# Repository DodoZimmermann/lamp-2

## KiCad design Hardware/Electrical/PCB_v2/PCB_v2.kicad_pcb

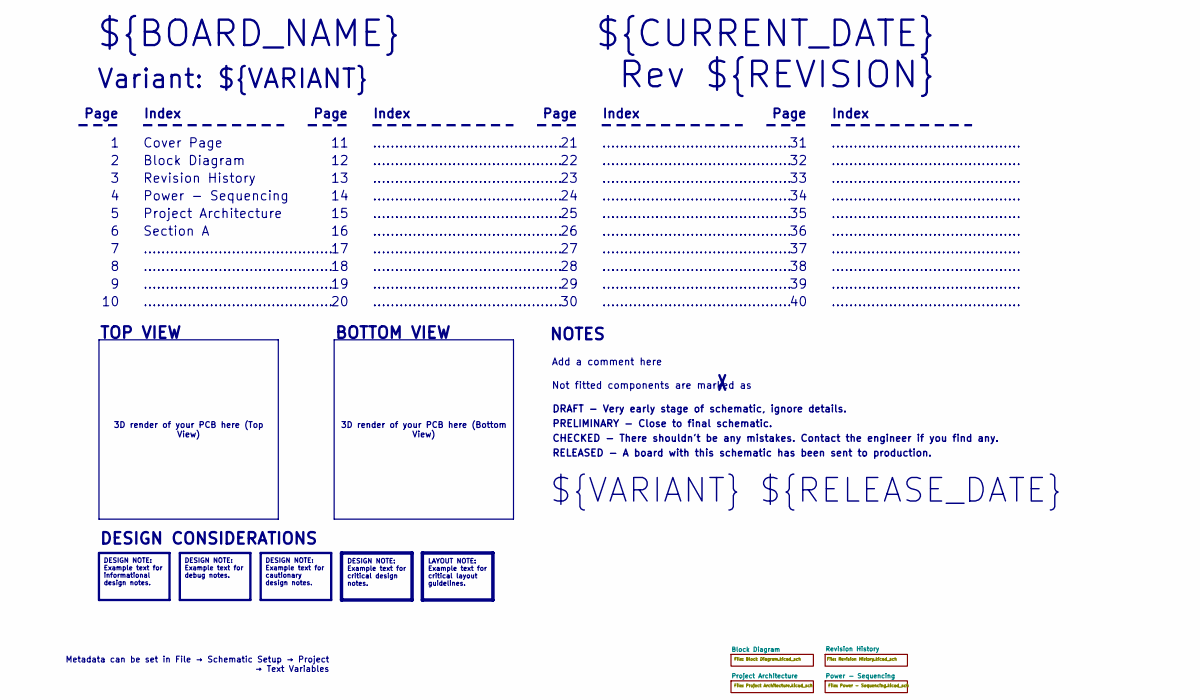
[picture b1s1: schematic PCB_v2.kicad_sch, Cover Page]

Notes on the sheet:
BOTTOM VIEW
...........................................
RELEASED - A board with this schematic has been sent to production.
Page
TOP VIEW
Not fitted components are marked as
Index
PRELIMINARY - Close to final schematic.
${VARIANT} ${RELEASE_DATE}
Power - Sequencing
${CURRENT_DATE}
Variant: ${VARIANT}
Rev ${REVISION}
Project Architecture
${BOARD_NAME}
DRAFT - Very early stage of schematic, ignore details.
Section A
Block Diagram
Add a comment here
Cover Page
NOTES
Revision History
CHECKED - There shouldn't be any mistakes. Contact the engineer if you find any.
DESIGN CONSIDERATIONS
3D render of your PCB here (Bottom View)
3D render of your PCB here (Top View)
Metadata can be set in File → Schematic Setup → Project → Text Variables
DESIGN NOTE: Example text for informational design notes.
LAYOUT NOTE: Example text for critical layout guidelines.
DESIGN NOTE: Example text for cautionary design notes.
DESIGN NOTE: Example text for debug notes.
DESIGN NOTE: Example text for critical design notes.

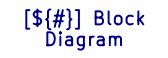
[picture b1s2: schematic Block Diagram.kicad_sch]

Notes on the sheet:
[${#}] ${TITLE}

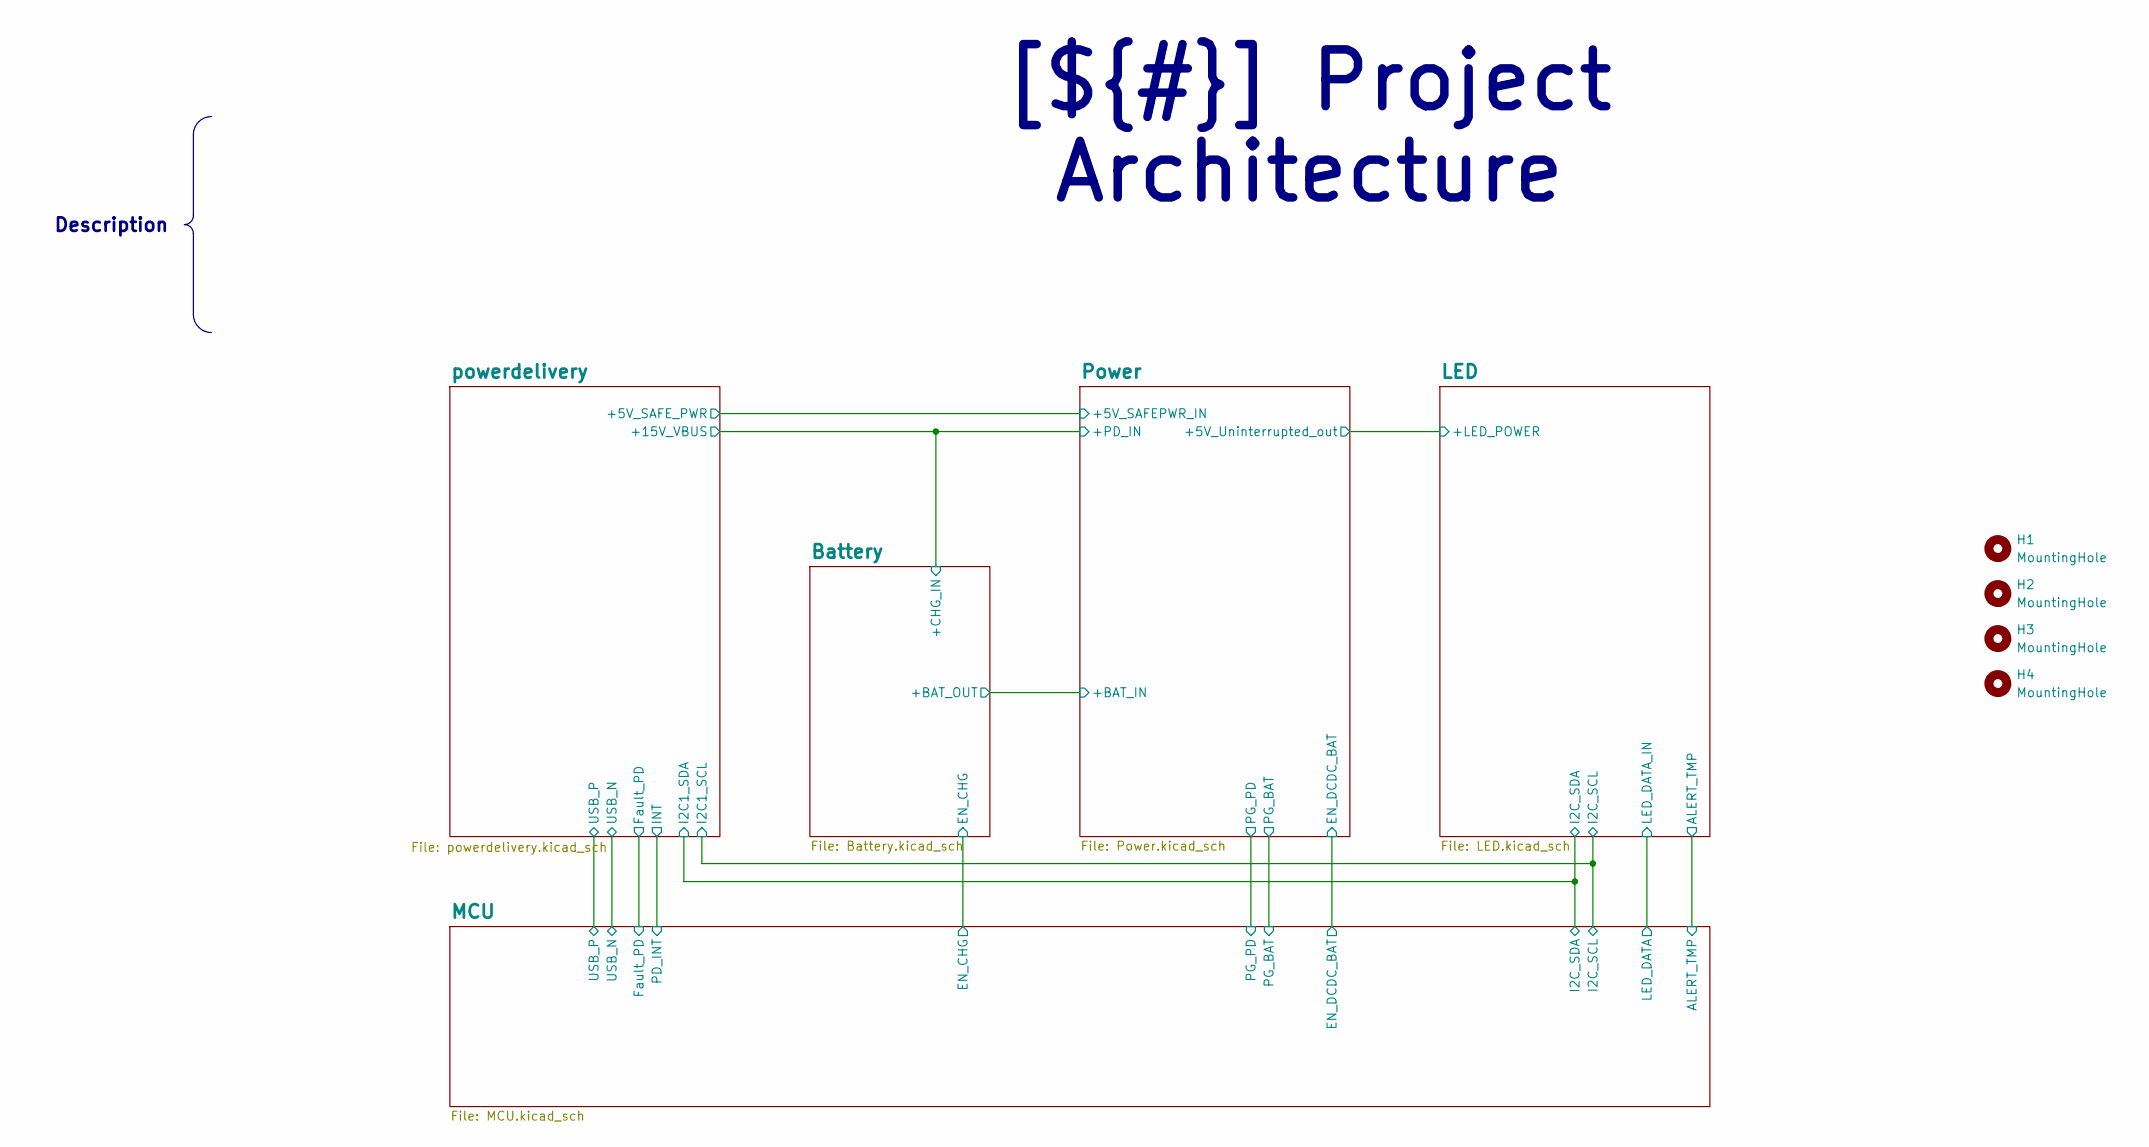
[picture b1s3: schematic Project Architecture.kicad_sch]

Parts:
H1, H2, H3, H4: MountingHole; MountingHole_2.7mm_M2.5

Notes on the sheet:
Description
[${#}] ${TITLE}

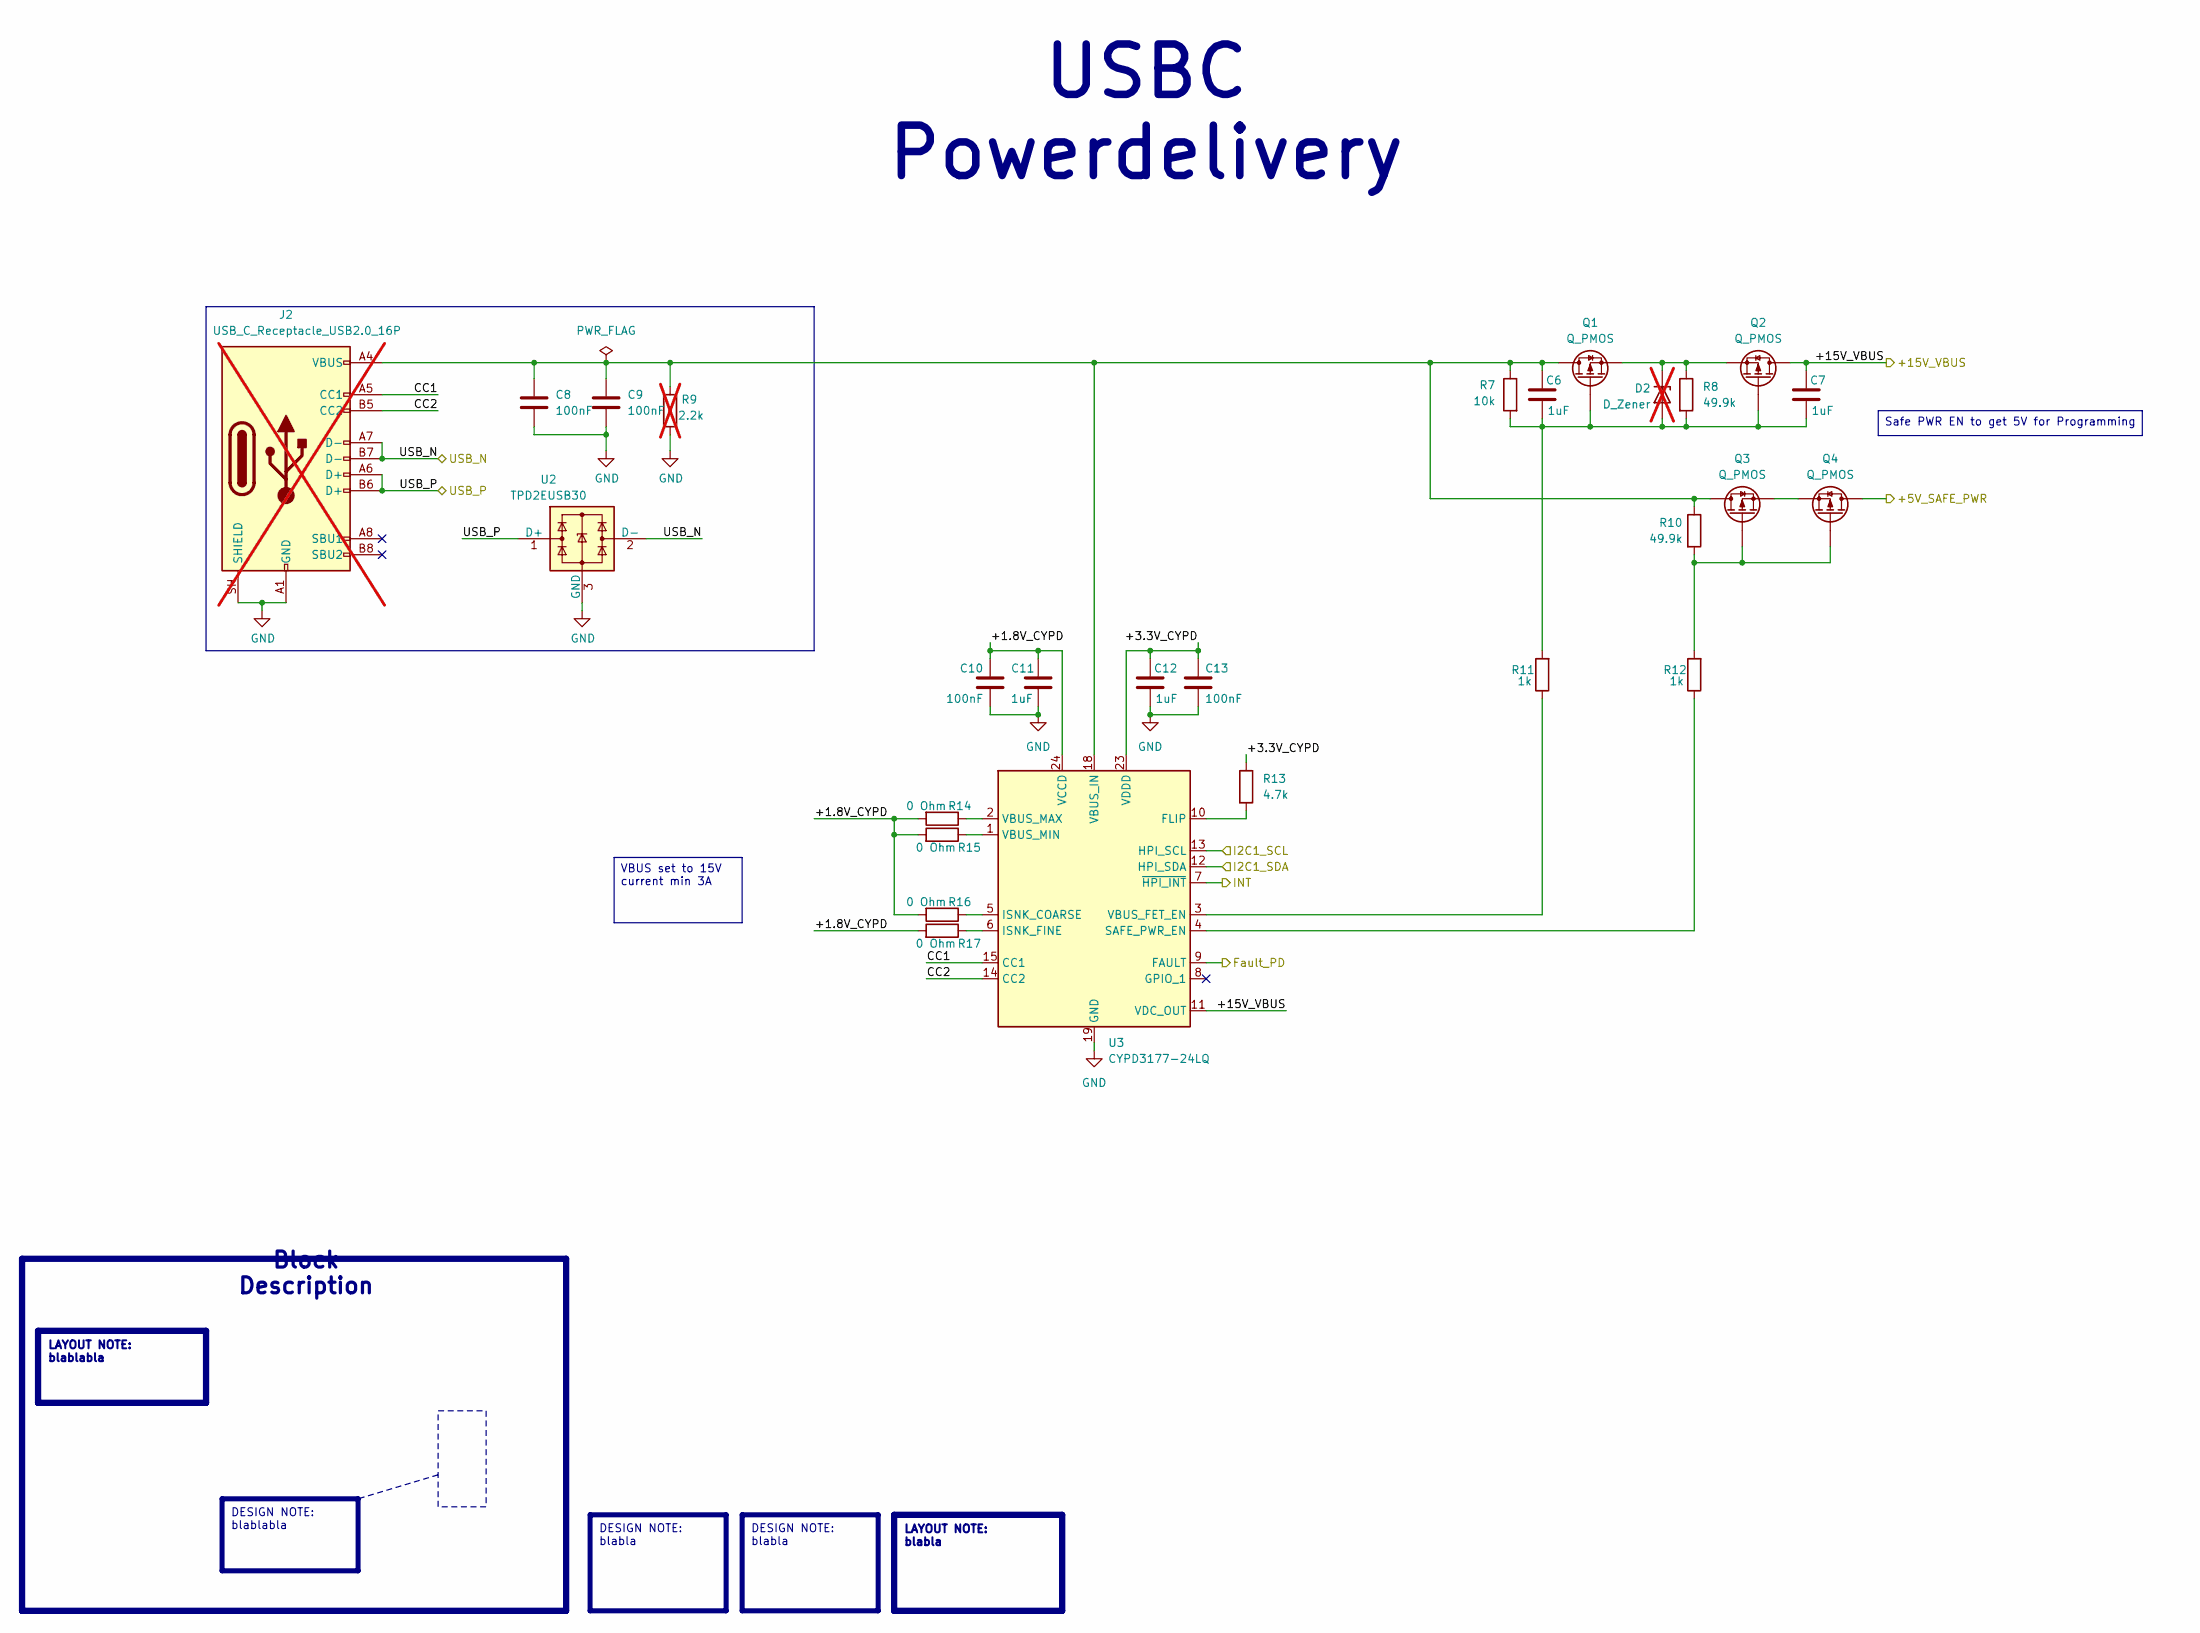
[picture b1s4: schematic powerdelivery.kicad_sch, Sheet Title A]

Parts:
C6, C7, C11, C12: 1uF; C_0603_1608Metric; Manufacturer Part Number CC0603KRX7R9BB105; LCSC Part # C15849
C8, C9, C10, C13: 100nF; C_0603_1608Metric; Manufacturer Part Number 885012206095; LCSC Part # C14663
D2: D_Zener; D_SOD-323; not fitted
J2: USB_C_Receptacle_USB2.0_16P; USB_C_Receptacle_GCT_USB4105-xx-A_16P_TopMnt_Horizontal; Manufacturer Part Number USB4105-GF-A; not fitted
Q1, Q2, Q3, Q4: Q_PMOS; PowerPAK_SO-8; Manufacturer Part Number SI7149ADP-T1-GE3; LCSC Part # C554002
R7: 10k; R_0603_1608Metric; Manufacturer Part Number ERJ-PB3B1002V; LCSC Part # C25804
R8, R10: 49.9k; R_0603_1608Metric; LCSC Part # C23184
R9: 2.2k; R_0603_1608Metric; Manufacturer Part Number RC0603FR-072K2L; LCSC Part # C114662; not fitted
R11, R12: 1k; R_0603_1608Metric; Manufacturer Part Number RC0603FR-071KL; LCSC Part # C21190
R13: 4.7k; R_0603_1608Metric; LCSC Part # C23162
R14, R15, R16, R17: 0 Ohm; R_0603_1608Metric; Manufacturer Part Number RC0603JR-070RL; LCSC Part # C21189
U2: TPD2EUSB30; Texas_DRT-3; Manufacturer Part Number TPD2EUSB30ADRTR; LCSC Part # C97502
U3: CYPD3177-24LQ; QFN-24-1EP_4x4mm_P0.5mm_EP2.75x2.75mm; LCSC Part # C2959321

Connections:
/Project Architecture/LED/I2C_SCL: U3.13 (HPI_SCL); also elsewhere on the board
/Project Architecture/LED/I2C_SDA: U3.12 (HPI_SDA); also elsewhere on the board
/Project Architecture/MCU/Fault_PD: U3.9 (FAULT); also elsewhere on the board
/Project Architecture/MCU/PD_INT: U3.7 (~HPI_INT); also elsewhere on the board
/Project Architecture/Power/+5V_SAFEPWR_IN: Q4.D; also elsewhere on the board
/Project Architecture/powerdelivery/+1.8V_CYPD: C10.2, C11.2, R14.2, R15.2, R16.2, R17.2, U3.24 (VCCD)
/Project Architecture/powerdelivery/+3.3V_CYPD: C12.2, C13.2, R13.1, U3.23 (VDDD)
/Project Architecture/powerdelivery/+15V_VBUS: C7.2, Q2.D, U3.11 (VDC_OUT); also elsewhere on the board
/Project Architecture/powerdelivery/CC1: J2.A5 (CC1), U3.15 (CC1)
/Project Architecture/powerdelivery/CC2: J2.B5 (CC2), U3.14 (CC2)
/Project Architecture/powerdelivery/USB_N: J2.A7 (D-), J2.B7 (D-), U2.2 (D-); also elsewhere on the board
/Project Architecture/powerdelivery/USB_P: J2.A6 (D+), J2.B6 (D+), U2.1 (D+); also elsewhere on the board
GND: C8.1, C9.1, C10.1, C11.1, C12.1, C13.1, J2.A1 (GND), J2.A12 (GND), J2.B1 (GND), J2.B12 (GND), J2.SH (SHIELD), R9.1, U2.3 (GND), U3.19 (GND), U3.22 (GND), U3.25 (GND); also elsewhere on the board
unnamed: C6.1, C7.1, D2.2 (A), Q1.G, Q2.G, R7.2, R8.2, R11.2
unnamed: D2.1 (K), Q1.S, Q2.S, R8.1
unnamed: Q3.G, Q4.G, R10.2, R12.2
unnamed: Q3.S, Q4.S
unnamed: R13.2, U3.10 (FLIP)
unnamed: R16.1, U3.5 (ISNK_COARSE)
unnamed: R17.1, U3.6 (ISNK_FINE)
unnamed: R12.1, U3.4 (SAFE_PWR_EN)
unnamed: R11.1, U3.3 (VBUS_FET_EN)
unnamed: C6.2, C8.2, C9.2, J2.A4 (VBUS), J2.A9 (VBUS), J2.B4 (VBUS), J2.B9 (VBUS), Q1.D, Q3.D, R7.1, R9.2, R10.1, U3.18 (VBUS_IN)
unnamed: R14.1, U3.2 (VBUS_MAX)
unnamed: R15.1, U3.1 (VBUS_MIN)

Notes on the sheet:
Block Description
DESIGN NOTE: blabla
LAYOUT NOTE: blablabla
USBC Powerdelivery
LAYOUT NOTE: blabla
Safe PWR EN to get 5V for Programming
DESIGN NOTE: blablabla
VBUS set to 15V current min 3A

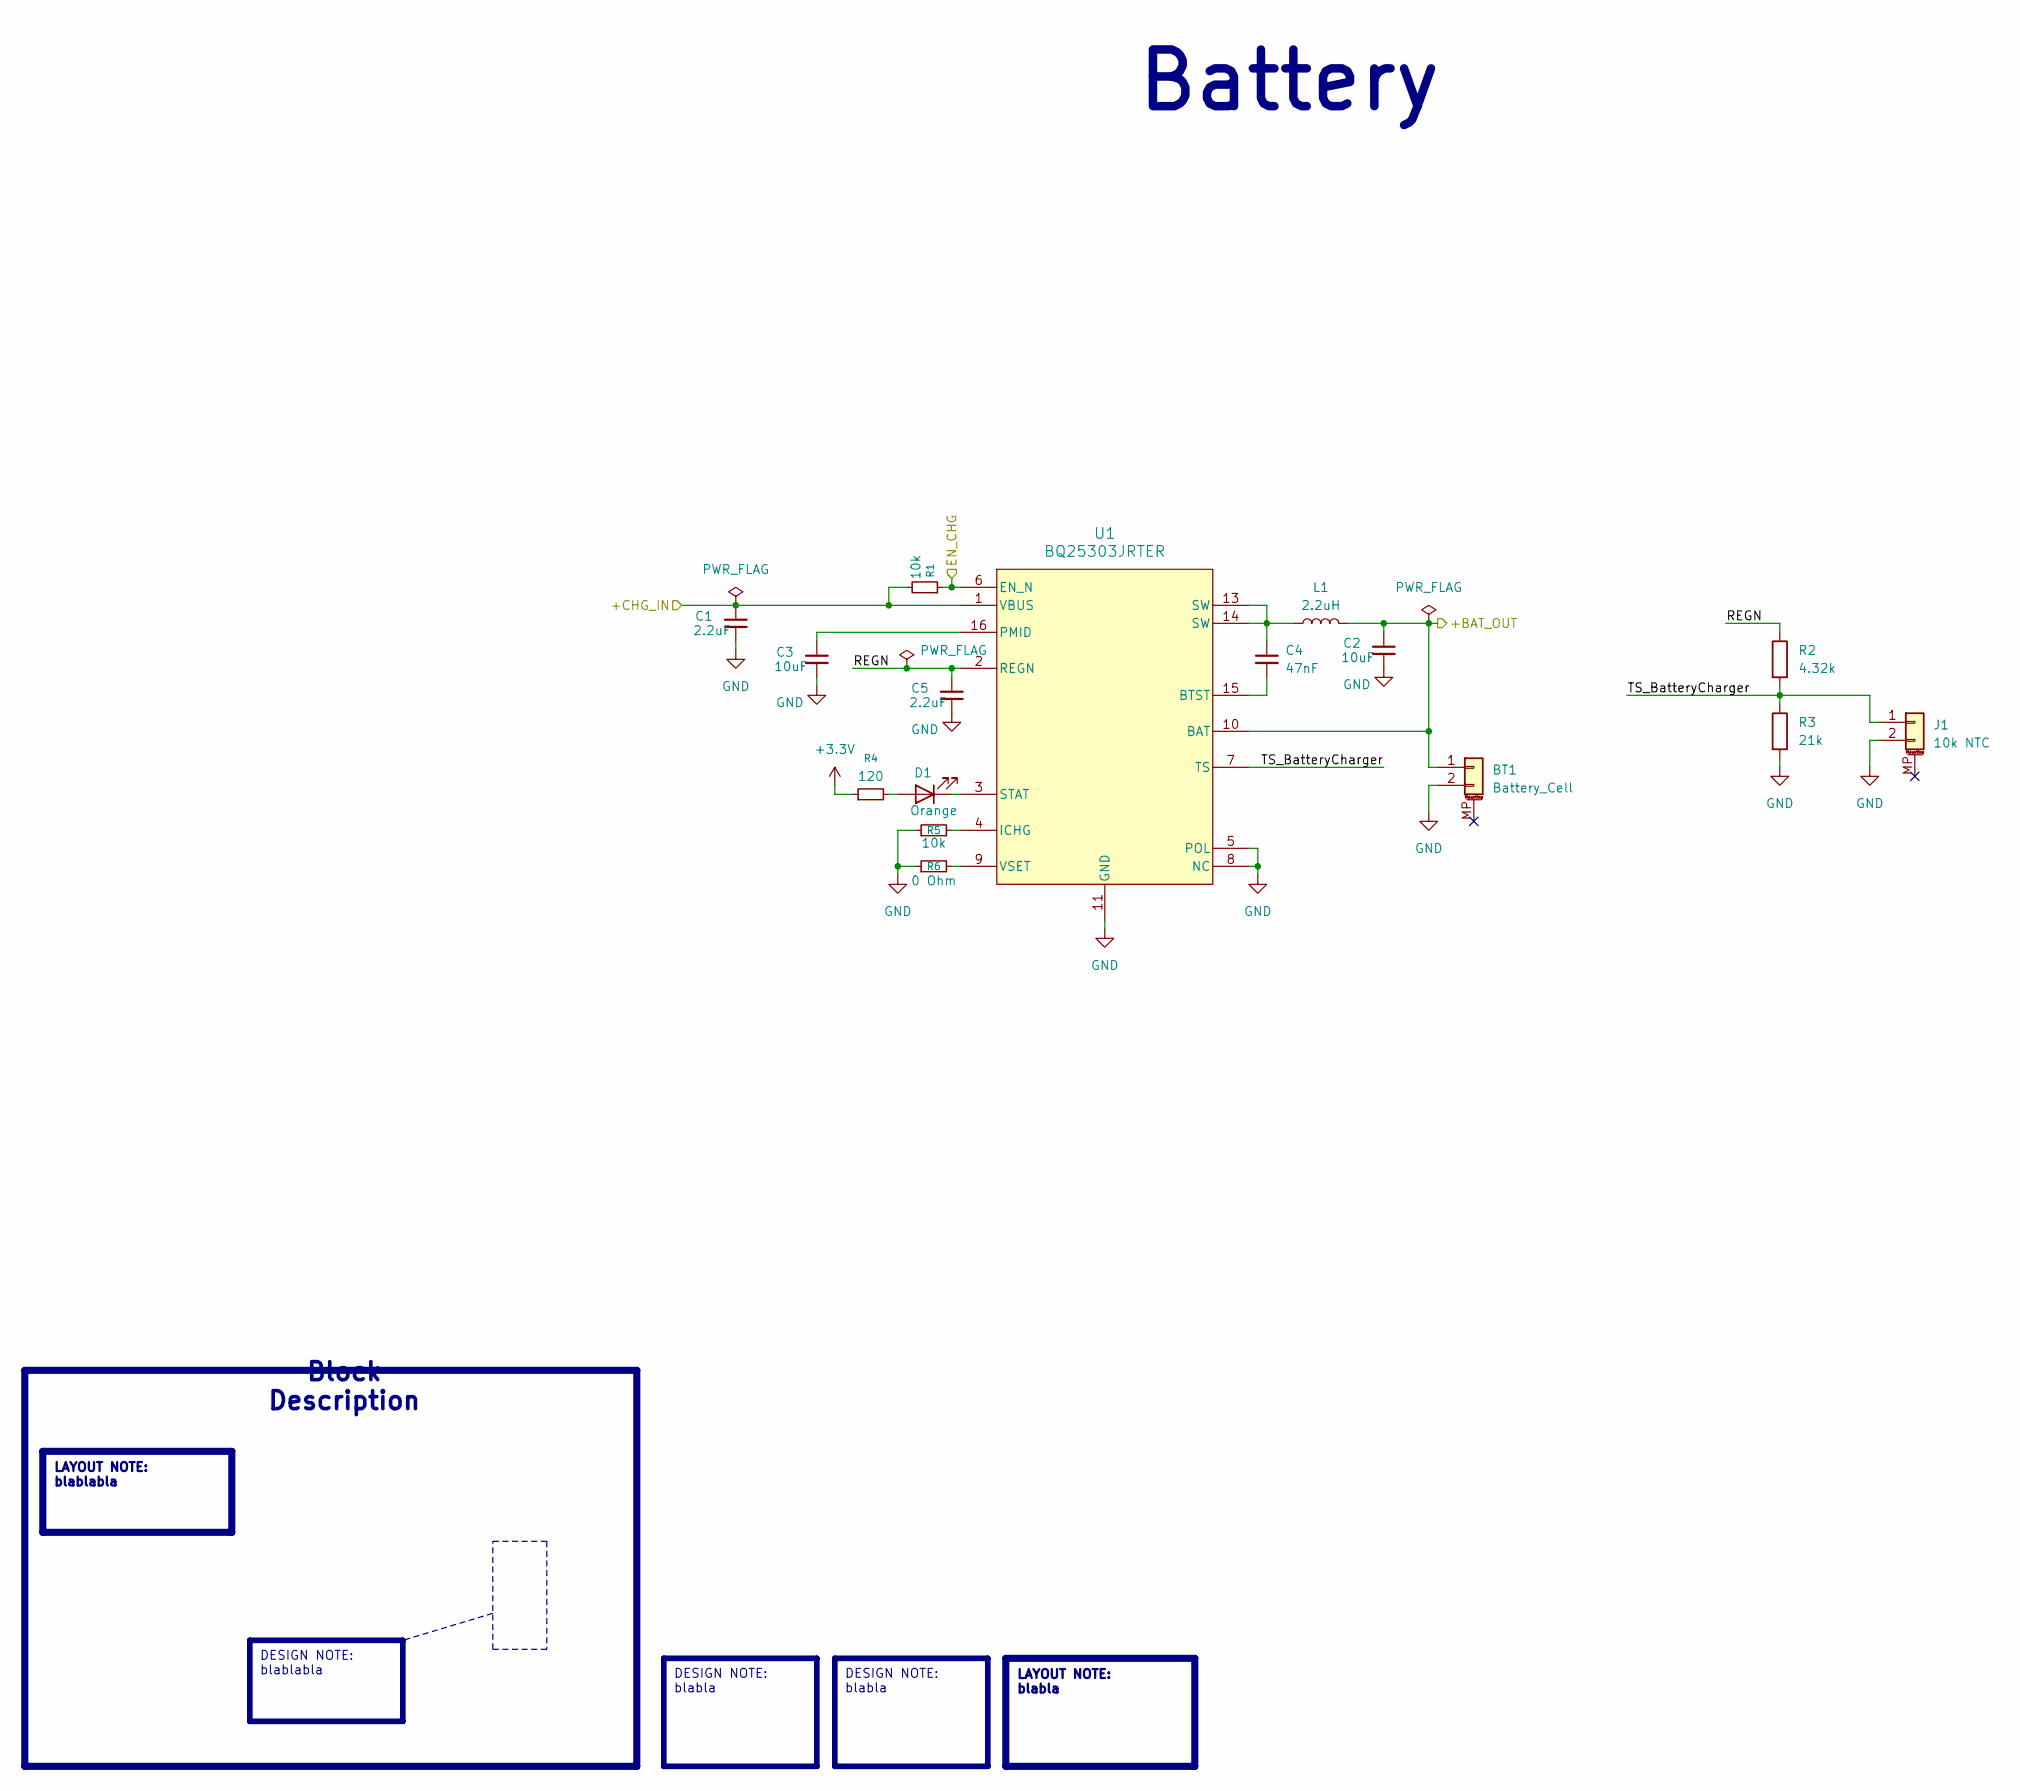
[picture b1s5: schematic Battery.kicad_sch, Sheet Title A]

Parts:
BT1: Battery_Cell; Molex_Micro-Fit_3.0_43650-0224_1x02-1MP_P3.00mm_Vertical; LCSC Part # C122425
C1, C5: 2.2uF; C_0603_1608Metric; LCSC Part # C23630
C2, C3: 10uF; C_1206_3216Metric; LCSC Part # C13585
C4: 47nF; C_0603_1608Metric; LCSC Part # C1622
D1: Orange; LED_0603_1608Metric; LCSC Part # C2286
J1: 10k NTC; JST_SH_BM02B-SRSS-TB_1x02-1MP_P1.00mm_Vertical; LCSC Part # C160388
L1: 2.2uH; L_Bourns_SRP5030T; LCSC Part # C2847475
R1, R5: 10k; R_0603_1608Metric; LCSC Part # C25804
R2: 4.32k; R_0603_1608Metric; LCSC Part # C23158
R3: 21k; R_0603_1608Metric; LCSC Part # C137769
R4: 120; R_0603_1608Metric; LCSC Part # C22765
R6: 0 Ohm; R_0603_1608Metric; LCSC Part # C21189
U1: BQ25303JRTER; WQFN-16-1EP_3x3mm_P0.5mm_EP1.68x1.68mm; LCSC Part # C2842775

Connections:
+3.3V: R4.1; also elsewhere on the board
/Project Architecture/Battery/+BAT_OUT: BT1.1, C2.1, L1.2, U1.10 (BAT); also elsewhere on the board
/Project Architecture/Battery/EN_CHG: R1.1, U1.6 (EN_N); also elsewhere on the board
/Project Architecture/Battery/REGN: C5.1, R2.1, U1.2 (REGN)
/Project Architecture/Battery/TS_BatteryCharger: J1.1, R2.2, R3.1, U1.7 (TS)
/Project Architecture/powerdelivery/+15V_VBUS: C1.1, R1.2, U1.1 (VBUS); also elsewhere on the board
GND: BT1.2, C1.2, C2.2, C3.2, C5.2, J1.2, R3.2, R5.1, R6.1, U1.5 (POL), U1.8 (NC), U1.11 (GND), U1.12 (GND), U1.17 (PAD); also elsewhere on the board
unnamed: C4.1, L1.1, U1.13 (SW), U1.14 (SW)
unnamed: D1.2 (A), R4.2
unnamed: D1.1 (K), U1.3 (STAT)
unnamed: C4.2, U1.15 (BTST)
unnamed: R5.2, U1.4 (ICHG)
unnamed: C3.1, U1.16 (PMID)
unnamed: R6.2, U1.9 (VSET)

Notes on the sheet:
Battery
LAYOUT NOTE: blablabla
DESIGN NOTE: blabla
Block Description
LAYOUT NOTE: blabla
DESIGN NOTE: blablabla

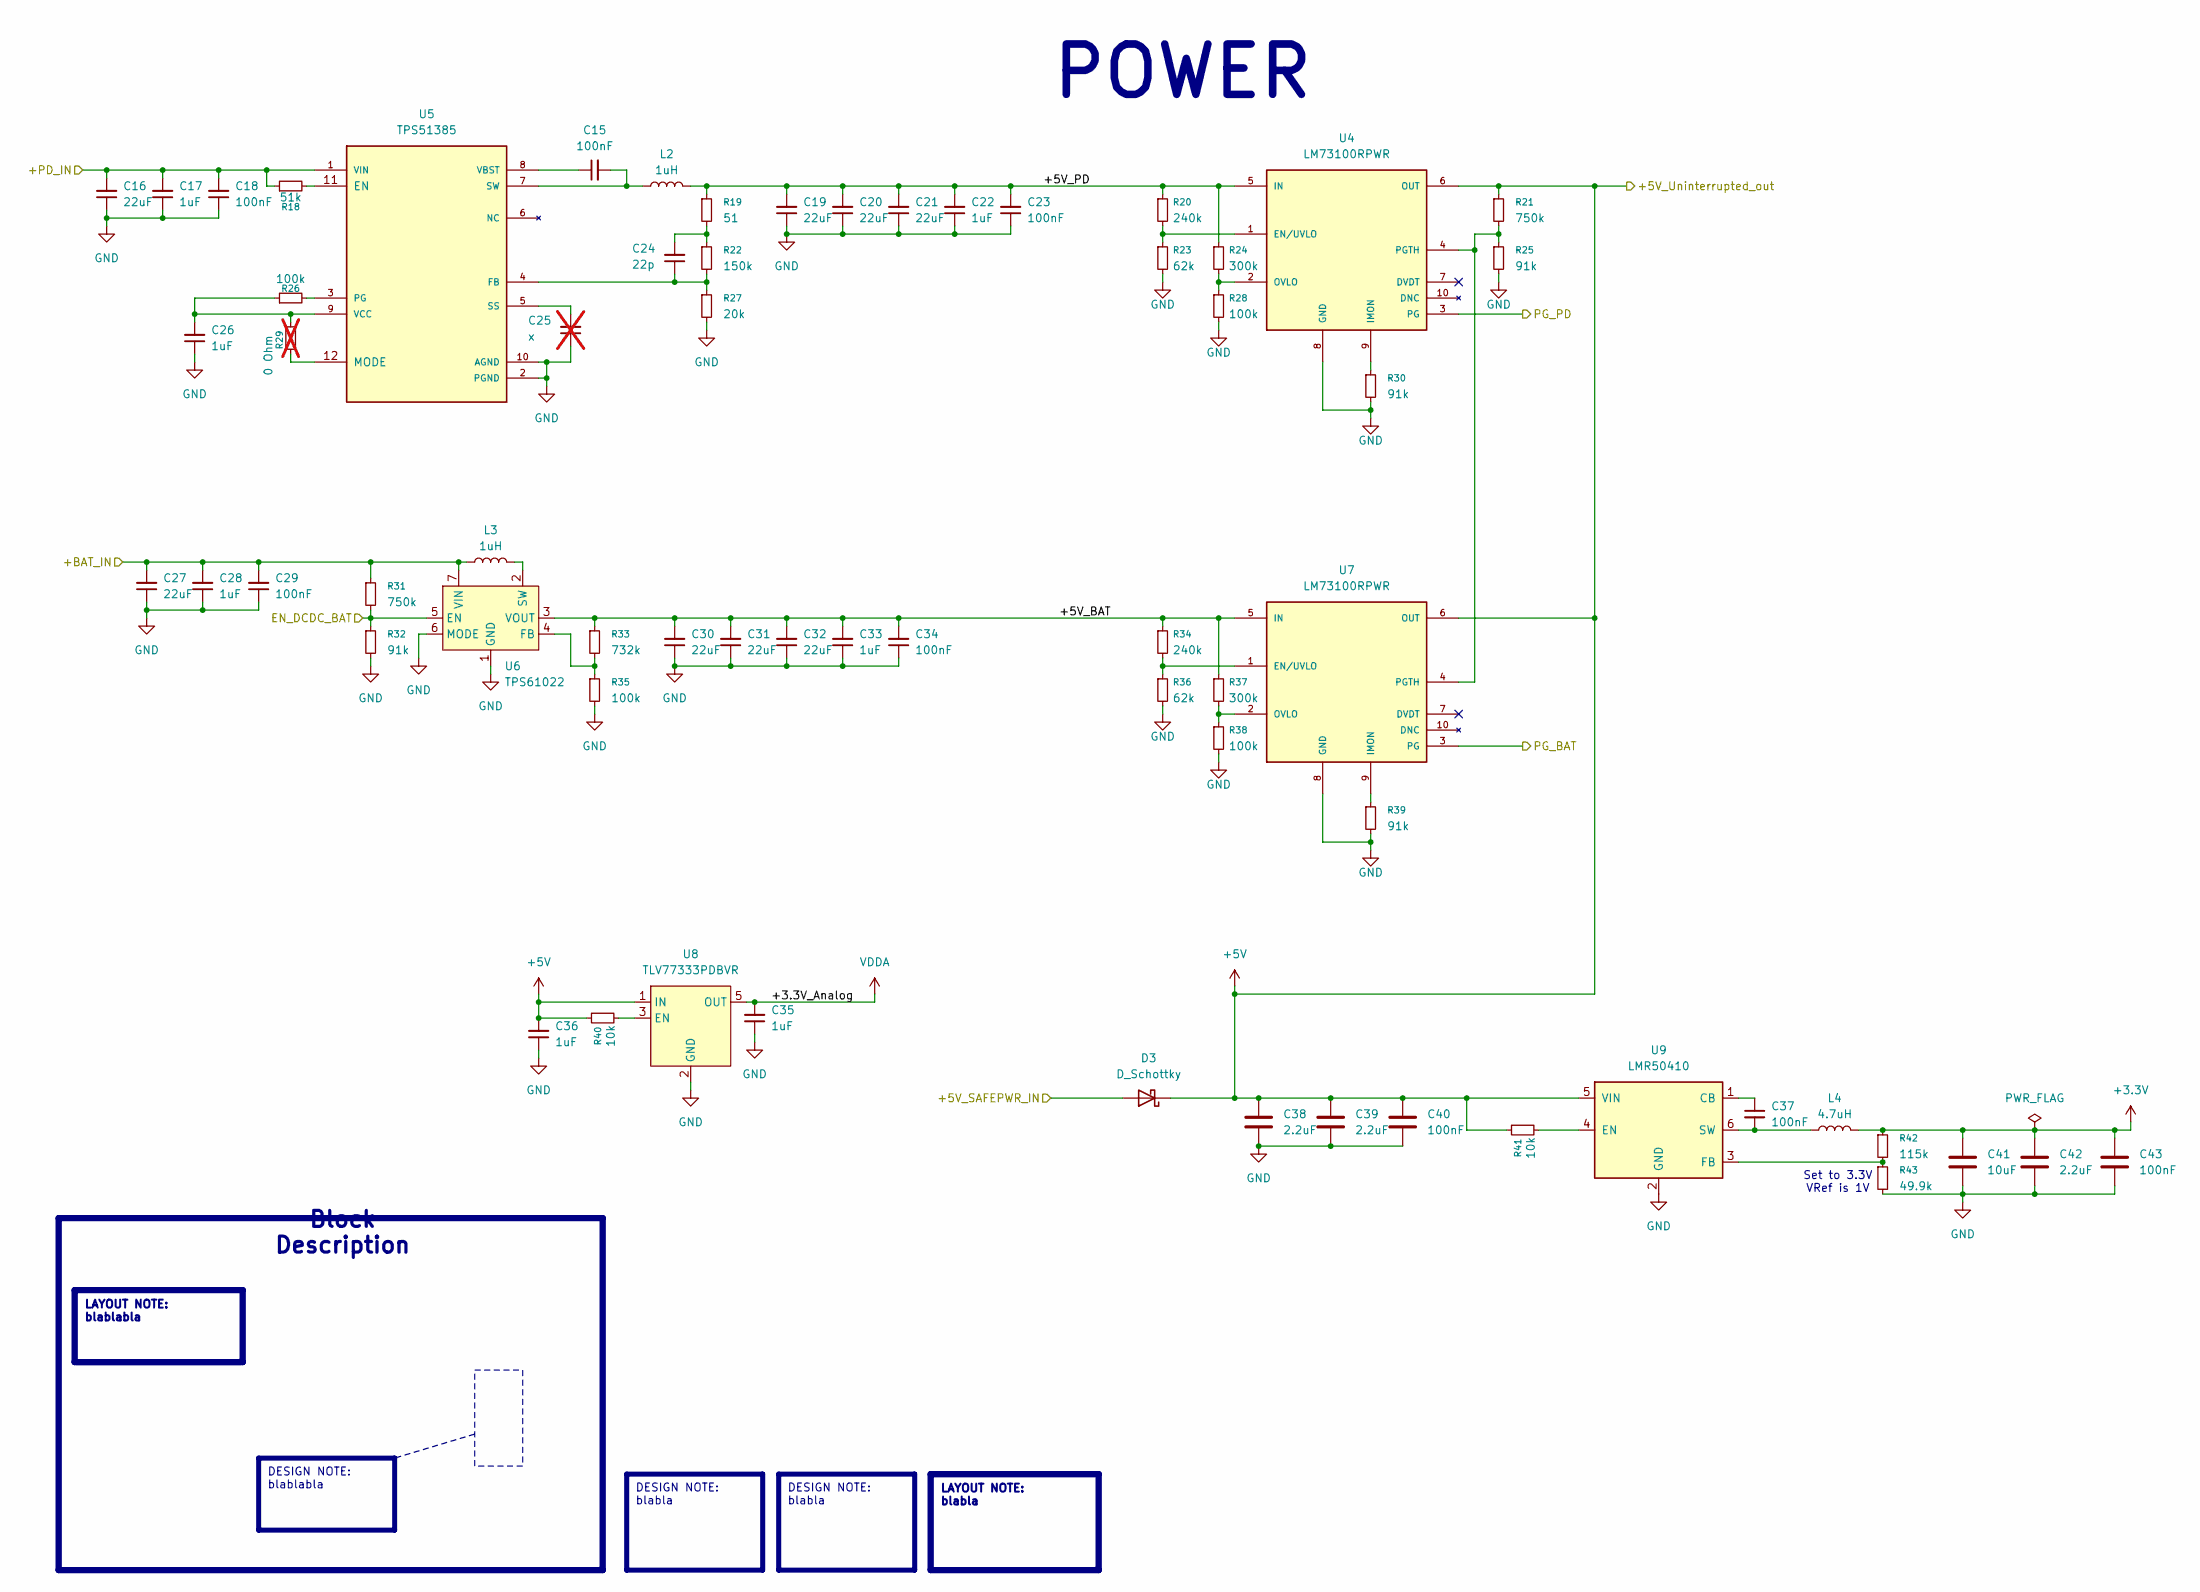
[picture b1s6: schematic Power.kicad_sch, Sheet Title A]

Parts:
C15, C18, C23, C29, C34, C37, C40, C43: 100nF; C_0603_1608Metric; LCSC Part # C14663
C16, C19, C20, C21, C27, C30, C31, C32: 22uF; C_1206_3216Metric; LCSC Part # C12891
C17, C22, C26, C28, C33, C35, C36: 1uF; C_0603_1608Metric; LCSC Part # C15849
C24: 22p; C_0603_1608Metric; LCSC Part # C1653
C25: x; C_0603_1608Metric; not fitted
C38, C39, C42: 2.2uF; C_0603_1608Metric; LCSC Part # C23630
C41: 10uF; C_1206_3216Metric; LCSC Part # C13585
D3: D_Schottky; SOT-23; LCSC Part # C2135
L2, L3: 1uH; L_Bourns_SRP7028A_7.3x6.6mm; LCSC Part # C2847480
L4: 4.7uH; L_Pulse_PA5402; LCSC Part # C553980
R18: 51k; R_0603_1608Metric; LCSC Part # C23196
R19: 51; R_0603_1608Metric; LCSC Part # C23197
R20, R34: 240k; R_0603_1608Metric; LCSC Part # C137765
R21, R31: 750k; R_0603_1608Metric; LCSC Part # C137684
R22: 150k; R_0603_1608Metric; LCSC Part # C22807
R23, R36: 62k; R_0603_1608Metric; LCSC Part # C137694
R24, R37: 300k; R_0603_1608Metric; LCSC Part # C23024
R25, R30, R32, R39: 91k; R_0603_1608Metric; LCSC Part # C23265
R26, R28, R35, R38: 100k; R_0603_1608Metric; LCSC Part # C25803
R27: 20k; R_0603_1608Metric; LCSC Part # C4184
R29: 0 Ohm; R_0603_1608Metric; not fitted
R33: 732k; R_0603_1608Metric; LCSC Part # C246003
R40, R41: 10k; R_0603_1608Metric; LCSC Part # C25804
R42: 115k; R_0603_1608Metric; LCSC Part # C22783
R43: 49.9k; R_0603_1608Metric; LCSC Part # C23184
U4, U7: LM73100RPWR; IC_LM73100RPWR; PARTREV 08/2019; LCSC Part # C3210761
U5: TPS51385; VREG_TPS51386RJNR; LCSC Part # C22418767
U6: TPS61022; Texas_RWU0007A_VQFN-7_2x2mm_P0.5mm; LCSC Part # C915088
U8: TLV77333PDBVR; SOT-23-5; LCSC C32445874
U9: LMR50410; SOT-23-6; LCSC Part # C2841056

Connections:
+3.3V: C41.1, C42.1, C43.1, L4.2, R42.1; also elsewhere on the board
+5V: C36.2, C38.1, C39.1, C40.1, D3.3 (K), R21.1, R40.1, R41.1, U4.6 (OUT), U7.6 (OUT), U8.1 (IN), U9.5 (VIN); also elsewhere on the board
/Project Architecture/Battery/+BAT_OUT: C27.2, C28.2, C29.2, L3.1, R31.1, U6.7 (VIN); also elsewhere on the board
/Project Architecture/MCU/EN_DCDC_BAT: R31.2, R32.1, U6.5 (EN); also elsewhere on the board
/Project Architecture/MCU/PG_BAT: U7.3 (PG); also elsewhere on the board
/Project Architecture/MCU/PG_PD: U4.3 (PG); also elsewhere on the board
/Project Architecture/Power/+5V_BAT: C30.2, C31.2, C32.2, C33.2, C34.2, R33.1, R34.1, R37.1, U6.3 (VOUT), U7.5 (IN)
/Project Architecture/Power/+5V_PD: C19.2, C20.2, C21.2, C22.2, C23.2, L2.2, R19.1, R20.1, R24.1, U4.5 (IN)
/Project Architecture/Power/+5V_SAFEPWR_IN: D3.1 (A), D3.2 (A); also elsewhere on the board
/Project Architecture/powerdelivery/+15V_VBUS: C16.2, C17.2, C18.2, R18.1, U5.1 (VIN); also elsewhere on the board
GND: C16.1, C17.1, C18.1, C19.1, C20.1, C21.1, C22.1, C23.1, C25.1, C26.1, C27.1, C28.1, C29.1, C30.1, C31.1, C32.1, C33.1, C34.1, C35.1, C36.1, C38.2, C39.2, C40.2, C41.2, C42.2, C43.2, R23.2, R25.2, R27.2, R28.2, R30.2, R32.2, R35.2, R36.2, R38.2, R39.2, R43.2, U4.8 (GND), U5.2 (PGND), U5.10 (AGND), U6.1 (GND), U6.6 (MODE), U7.8 (GND), U8.2 (GND), U8.4 (NC), U9.2 (GND); also elsewhere on the board
unnamed: C24.2, R19.2, R22.1
unnamed: R20.2, R23.1, U4.1 (EN/UVLO)
unnamed: R30.1, U4.9 (IMON)
unnamed: R24.2, R28.1, U4.2 (OVLO)
unnamed: R21.2, R25.1, U4.4 (PGTH), U7.4 (PGTH)
unnamed: R18.2, U5.11 (EN)
unnamed: C24.1, R22.2, R27.1, U5.4 (FB)
unnamed: R29.1, U5.12 (MODE)
unnamed: R26.2, U5.3 (PG)
unnamed: C25.2, U5.5 (SS)
unnamed: C15.2, L2.1, U5.7 (SW)
unnamed: C15.1, U5.8 (VBST)
unnamed: C26.2, R26.1, R29.2, U5.9 (VCC)
unnamed: R33.2, R35.1, U6.4 (FB)
unnamed: L3.2, U6.2 (SW)
unnamed: R34.2, R36.1, U7.1 (EN/UVLO)
unnamed: R39.1, U7.9 (IMON)
unnamed: R37.2, R38.1, U7.2 (OVLO)
unnamed: R40.2, U8.3 (EN)
unnamed: C37.1, U9.1 (CB)
unnamed: R41.2, U9.4 (EN)
unnamed: R42.2, R43.1, U9.3 (FB)
unnamed: C37.2, L4.1, U9.6 (SW)
VDDA: C35.2, U8.5 (OUT); also elsewhere on the board

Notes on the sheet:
Set to 3.3V VRef is 1V
LAYOUT NOTE: blabla
POWER
DESIGN NOTE: blabla
DESIGN NOTE: blablabla
LAYOUT NOTE: blablabla
Block Description
